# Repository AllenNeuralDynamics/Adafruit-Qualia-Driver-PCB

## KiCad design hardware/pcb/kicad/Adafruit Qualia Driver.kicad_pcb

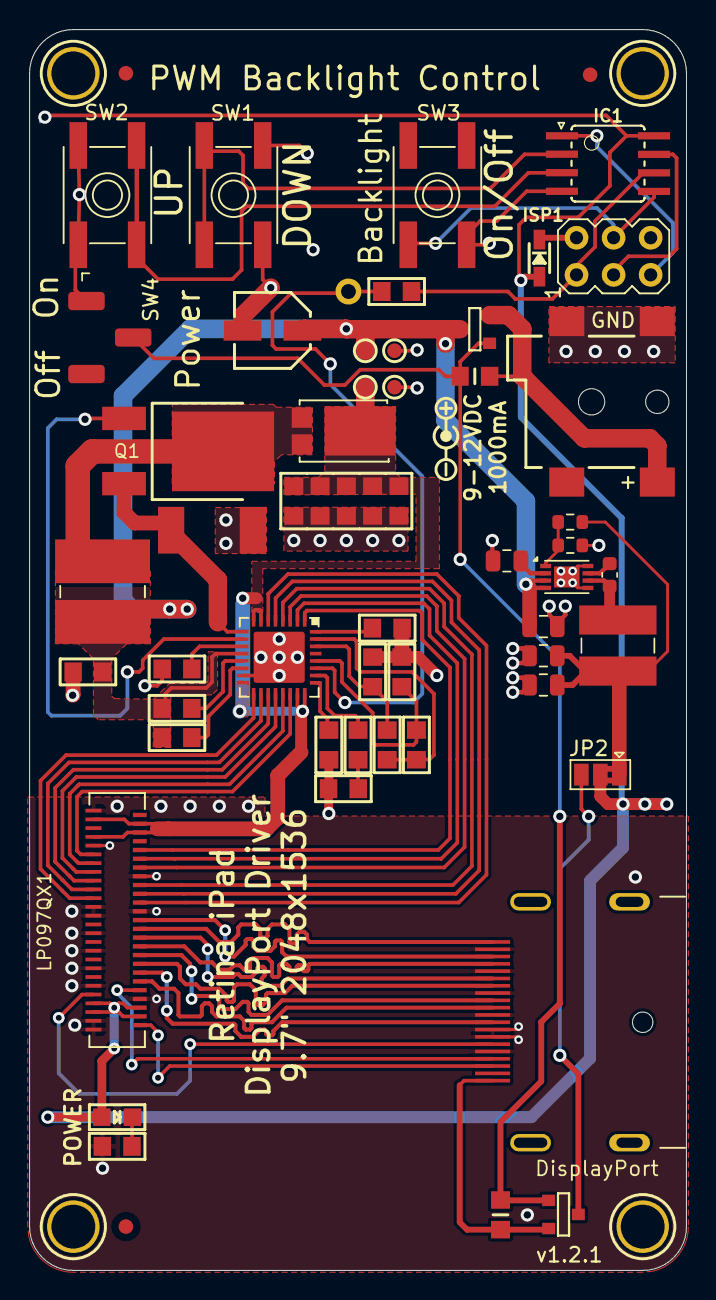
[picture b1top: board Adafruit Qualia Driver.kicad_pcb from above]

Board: 2 copper layers, 45.0 x 85.0 mm, 63 parts (0 on the bottom side), 58 nets.

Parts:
C1: 10uF; _0805
C2: 4.7uF; _0805
C3: 4.7nF; _0805
C4, C5, C6, C7, C8: 4.7uF/50V; _0805
C16: 47uF 25V; PANASONIC_C
C17, C19, C21: 10uF; C_0805_2012Metric
C18: 0.1uF; C_0603_1608Metric
C20: 1uF; C_0805_2012Metric
D1: PDS560-13; POWERDI-5
D2: 1N4148; SOD-323
FID1, FID2, FID3: FIDUCIAL; Fiducial_1mm_Mask2mm
IC1: ATTINY85S; SOIC8
ISP1: AVRISP-6; AVRISP
JP1: PINHD-1X1CB; 1X01-CLEANBIG
JP2: Jumper_3_Bridged12; SolderJumper-3_P1.3mm_Bridged2Bar12_Pad1.0x1.5mm
L1: 22uH; INDUCTOR_6X6MM_SUMIDA_CDRH5D28
L3: 15uH; L_Wuerth_5.5x5.3mm
LED1: green; CHIPLED_0805
Q1: IRLR024NTRPBF; DPAK
R1: 470; _0805
R2, R3: 100K; _0805
R4, R9, R14: 20K; _0805
R5: 27K; _0805
R6, R7: 20K; _0805MP
R8, R10: 47K; _0805
R11: 15K; _0805
R12: 7.5K; _0805
R13: 0.058; 2512
R15: 10K; R_0603_1608Metric
R16: 31K6; R_0603_1608Metric
SW1, SW2, SW3: SPST_TACT-EVQQ2; EVQ-Q2
SW4: SW_SPDT; SW_SPDT_CK_JS102011JCQN
T1, T2: IRLML2246; SOT-23
TP1, TP4: GND; TESTPOINT_ROUND_1MM
TP2: VIN; TESTPOINT_ROUND_1MM
TP3: 20V; TESTPOINT_ROUND_1MM
U1: LT3754; QFN32_5MM
U3: MCP16311x-xMNY; DFN-8-1EP_3x2mm_P0.5mm_EP1.75x1.45mm
U$10: SYMBOL_POSITIVE_CENTER-M
U$11, U$32, U$33, U$34: MOUNTINGHOLE3.0THIN; MOUNTINGHOLE_3.0_PLATEDTHIN
X1: 0472720001; DISPLAYPORT_0472720001
X2: 5047405100; FPC_51PIN_502250-5191_EXT
X3: 2.1mm; DCJACK_2MM_SMT

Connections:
3.3V: JP2.3 (B), T2.1 (D)
20V: C4.1, C5.1, C6.1, C7.1, C8.1, D1.C, TP3.P$1, U1.7 (LED7), U1.8 (LED8), U1.16 (VOUT), U1.23 (LED15), U1.24 (LED16), X2.45 (LEDB_A@1), X2.46 (LEDB_A@2), X2.48 (LEDA_A@1), X2.49 (LEDA_A@2)
/BDOWN: IC1.3 ((XTAL2/CLKO/OC1B/ADC2/PCINT4)PB4), SW2.B (S), SW2.B' (S1)
/BUP: IC1.2 ((XTAL1/CLKI/OC1B/ADC3/PCINT3)PB3), SW1.B (S), SW1.B' (S1)
/DPP: R6.2, T2.2 (S), X1.20 (DP_PWR)
/LEDK_A1: U1.1 (LED1), X2.42 (LEDA_K@1)
/LEDK_A2: U1.22 (LED14), X2.41 (LEDA_K@2)
/LEDK_A3: U1.2 (LED2), X2.40 (LEDA_K@3)
/LEDK_A4: U1.21 (LED13), X2.39 (LEDA_K@4)
/LEDK_A5: U1.3 (LED3), X2.38 (LEDA_K@5)
/LEDK_A6: U1.20 (LED12), X2.37 (LEDA_K@6)
/LEDK_B1: U1.19 (LED11), X2.35 (LEDB_K@1)
/LEDK_B2: U1.4 (LED4), X2.34 (LEDB_K@2)
/LEDK_B3: U1.18 (LED10), X2.33 (LEDB_K@3)
/LEDK_B4: U1.5 (LED5), X2.32 (LEDB_K@4)
/LEDK_B5: U1.17 (LED9), X2.31 (LEDB_K@5)
/LEDK_B6: U1.6 (LED6), X2.30 (LEDB_K@6)
/MISO: IC1.6 ((MISO/DO/AIN1/OC0B/OC1A/PCINT1)PB1), ISP1.1 (MISO), R14.1
/MOSI: IC1.5 ((MOSI/DI/SDA/AIN0/OC0A/OC1A/AREF/PCINT0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), ISP1.4 (MOSI), SW3.B (S)
/ON/OFF: R6.1, R7.1, SW4.2 (B), T1.3 (G), T2.3 (G)
/PWM: JP1.1, R14.2, U1.27 (PWM)
/RST: IC1.1 ((RESET/DW/ADC0/PCINT5)PB5), ISP1.5 (RST)
/SCLK: IC1.7 ((SCK/USCK/SCL/ADC1/T0/INT0/PCINT2)PB2), ISP1.3 (SCK)
GND: C1.2, C2.2, C3.2, C4.2, C5.2, C6.2, C7.2, C8.2, C16.-, C17.2, C19.2, C20.2, C21.2, IC1.4 (GND), ISP1.6 (GND), R1.2, R5.1, R9.1, R10.1, R11.1, R13.1, R15.2, SW1.A, SW1.A' (P1), SW2.A, SW2.A' (P1), SW3.A, SW4.1 (A), TP1.P$1, TP4.P$1, U1.15 (SYNC), U1.33 (GND), U3.5 (GND), U3.8 (GND), U3.9 (GND), X1.2 (GND@4), X1.5 (GND@3), X1.8 (GND@2), X1.11 (GND@1), X1.13 (CONFIG1), X1.14 (CONFIG2), X1.16 (GND@5), X2.1 (GND@1), X2.3 (GND@2), X2.8 (GND@3), X2.11 (GND@4), X2.15 (GND@5), X2.19 (GND@6), X2.23 (GND@7), X2.27 (GND@8), X2.28 (GND@9), X2.29 (GND@10), X2.36 (GND@11), X2.43 (GND@12), X2.51 (GND@13), X3.GND, X3.GNDBREAK
unnamed: C3.1, R12.1
unnamed: D2.C, ISP1.2 (VCC)
unnamed: C17.1, C21.1, JP2.1 (A), L3.2, R16.1
unnamed: D1.A1 (A), D1.A2 (A), L1.P$2 (2), Q1.4 (D)
unnamed: LED1.C, R1.1
unnamed: Q1.1 (G), U1.10 (GATE)
unnamed: Q1.3 (S), R13.2, U1.9 (SENSE)
unnamed: R7.2, T1.2 (S), X3.PWR
unnamed: R3.2, U1.14 (#FAULT)
unnamed: C2.1, U1.11 (INTVCC)
unnamed: R11.2, U1.32 (ISET)
unnamed: R8.1, R9.2, U1.28 (OVPSET)
unnamed: R10.2, U1.25 (RT)
unnamed: R2.1, U1.13 (SHDN/UVLO)
unnamed: R4.1, R5.2, U1.30 (TSET)
unnamed: R12.2, U1.26 (VC)
unnamed: R4.2, R8.2, U1.31 (VREF)
unnamed: C18.1, U3.7 (BOOST)
unnamed: C18.2, L3.1, U3.6 (SW)
unnamed: C20.1, U3.2 (V_{CC})
unnamed: R15.1, R16.2, U3.1 (Vfb)
unnamed: X1.15 (AUX+), X2.9 (AUX_P)
unnamed: X1.17 (AUX-), X2.10 (AUX_N)
unnamed: X1.18 (HOTPLUG), X2.2 (HOTPLUG)
unnamed: X1.12 (ML_LANE0+), X2.14 (LANE0_P)
unnamed: X1.10 (ML_LANE0-), X2.12 (LANE0_N)
unnamed: X1.9 (ML_LANE1+), X2.18 (LANE1_P)
unnamed: X1.7 (ML_LANE1-), X2.16 (LANE1_N)
unnamed: X1.6 (ML_LANE2+), X2.22 (LANE2_P)
unnamed: X1.4 (ML_LANE2-), X2.20 (LANE2_N)
unnamed: X1.3 (ML_LANE3+), X2.26 (LANE3_P)
unnamed: X1.1 (ML_LANE3-), X2.24 (LANE3_N)
VCC: D2.A, IC1.8 (VCC), JP2.2 (C), LED1.A, X2.4 (VCC@1), X2.5 (VCC@2), X2.6 (VCC@3), X2.7 (VCC@4)
VIN: C1.1, C16.+, C19.1, L1.P$1 (1), R2.2, R3.1, T1.1 (D), TP2.P$1, U1.12 (VIN), U3.3 (EN), U3.4 (V_{IN})

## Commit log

2024-10-03 update pcb silkscreen / origins
